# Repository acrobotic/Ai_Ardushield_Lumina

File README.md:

Overview
---
This repository includes the Eagle design files (schematics and layout) for our
[WS2812B RGB LED Shield for the Arduino Uno][1]. The shield design is based on the
popular WS2812 'smart' LED package, which contains an embedded, costant-current
LED driver (the WS2811).

The shield includes **40 WS2812B LEDs in a 5x8 array configuration**. But, contrary to a traditional
LED matrix, the shield uses a single data line (Digital Pin 8) from the 
Arduino to control brightness and color!  The shield also includes a power 
terminal for using an external supply.

The firmware files along with code samples are also included in this
repository.

Product page
---
Please consider buying products from Acrobotic to help fund future Open-Source
projects like this! We'll always put our best effort in every project, and
release all our design files and code for you to use.

[Tutorials, technical details, and more information about this product can be
found here: http://acrobotic.com/catalog/product/view/id/69][1]

On our store, we also [carry a 10-pack][2] of WS2812B RGB LEDs for you to use 
on your next project!

License Information
---

All contents of this repository are licensed under a [Creative Commons
Attribution-ShareAlike 3.0 Unported
License](http://creativecommons.org/licenses/by-sa/3.0/).

[1]: http://acrobotic.com/catalog/product/view/id/69 "Ardushield Lumina"
[2]: http://acrobotic.com/catalog/product/view/id/45 "WS2812B RGB LED - 10-Pack"

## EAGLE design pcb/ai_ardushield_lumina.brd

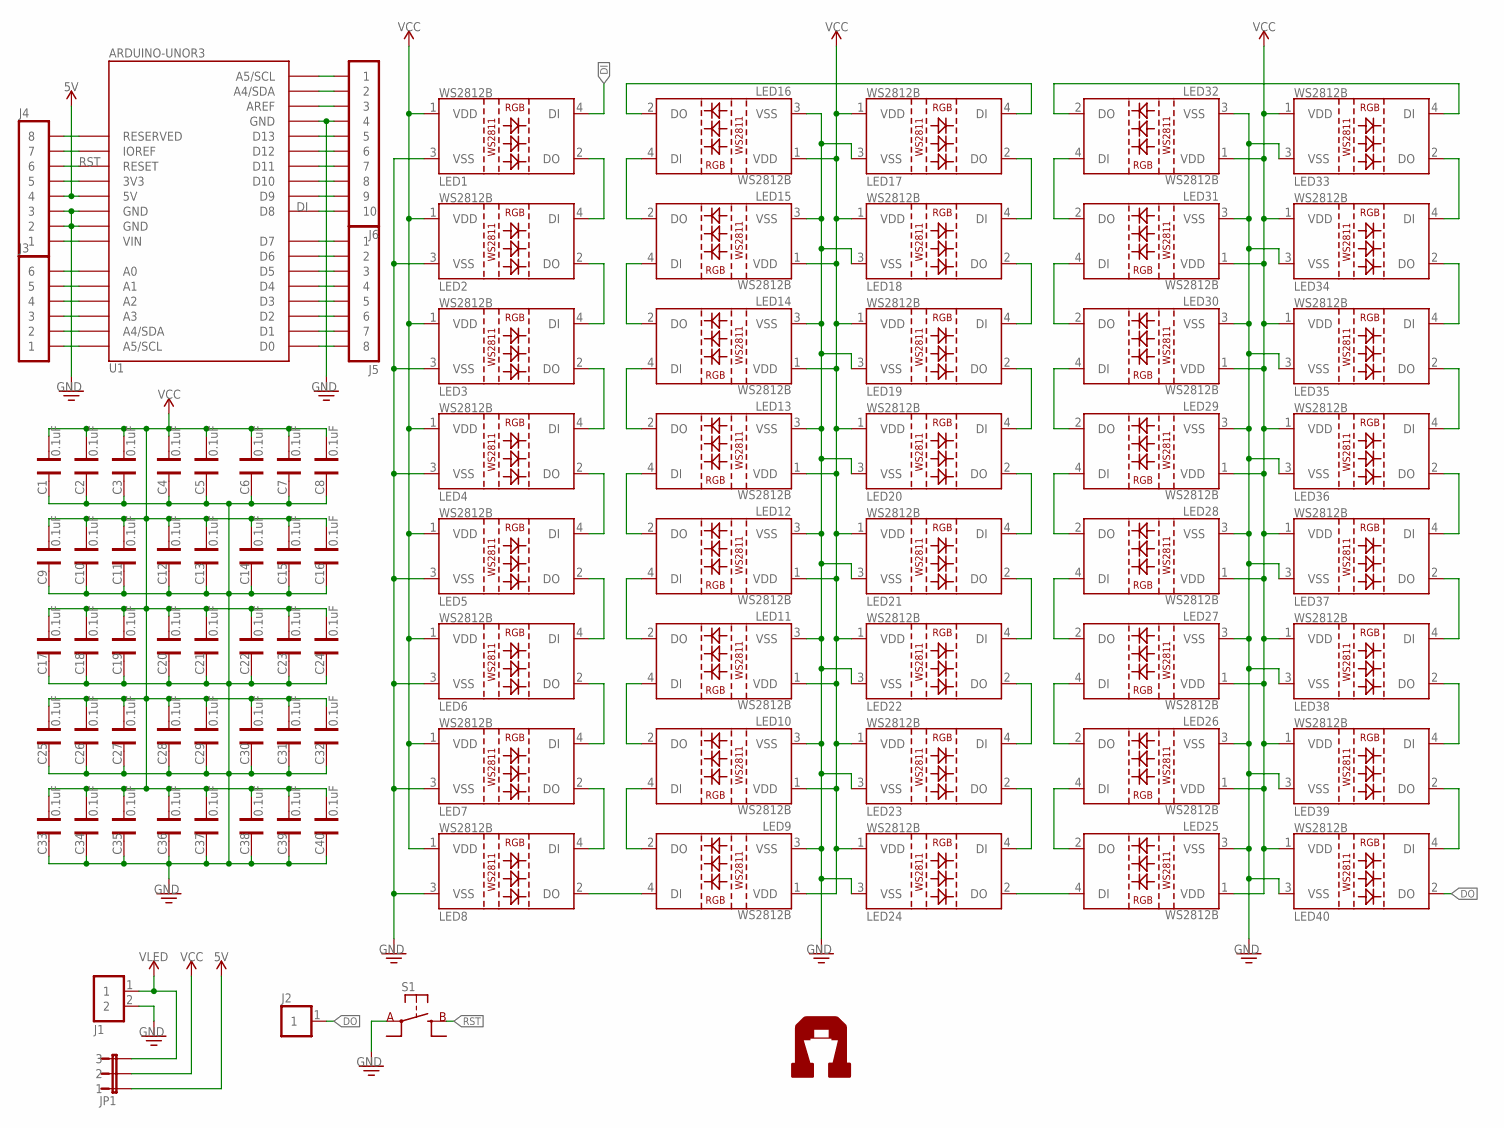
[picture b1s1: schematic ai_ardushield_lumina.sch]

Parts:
C1, C2, C3, C4, C5, C6, C7, C8, C9, C10, C11, C12, C13, C14, C15, C16, C17, C18, C19, C20, C21, C22, C23, C24, C25, C26, C27, C28, C29, C30, C31, C32, C33, C34, C35, C36, C37, C38, C39, C40: 0.1uF; CAP-0603
J1: 1X02ST; 1X02-ST
J2: 1X01
J3: 1X06
J4, J5: 1X08
J6: 1X10
JP1: 1X03-PJ; 1X03
LED1, LED2, LED3, LED4, LED5, LED6, LED7, LED8, LED9, LED10, LED11, LED12, LED13, LED14, LED15, LED16, LED17, LED18, LED19, LED20, LED21, LED22, LED23, LED24, LED25, LED26, LED27, LED28, LED29, LED30, LED31, LED32, LED33, LED34, LED35, LED36, LED37, LED38, LED39, LED40: LED-WS2812B
S1: SW-SPSTSMD06X06; SW-SPST-SMD06X06
U1: ARDUINOUNOR3-STRAIGHT; UNOR3-STRAIGHT
U$9: AI-LOGOL; AI-LOGO-L

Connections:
5V: J4.4, JP1.1, U1.5V
DI: J6.10, LED1.4 (DI), U1.D8
DO: J2.1, LED40.2 (DO)
GND: C1.2, C2.2, C3.2, C4.2, C5.2, C6.2, C7.2, C8.2, C9.2, C10.2, C11.2, C12.2, C13.2, C14.2, C15.2, C16.2, C17.2, C18.2, C19.2, C20.2, C21.2, C22.2, C23.2, C24.2, C25.2, C26.2, C27.2, C28.2, C29.2, C30.2, C31.2, C32.2, C33.2, C34.2, C35.2, C36.2, C37.2, C38.2, C39.2, C40.2, J1.2, J4.2, J4.3, J6.4, LED1.3 (VSS), LED2.3 (VSS), LED3.3 (VSS), LED4.3 (VSS), LED5.3 (VSS), LED6.3 (VSS), LED7.3 (VSS), LED8.3 (VSS), LED9.3 (VSS), LED10.3 (VSS), LED11.3 (VSS), LED12.3 (VSS), LED13.3 (VSS), LED14.3 (VSS), LED15.3 (VSS), LED16.3 (VSS), LED17.3 (VSS), LED18.3 (VSS), LED19.3 (VSS), LED20.3 (VSS), LED21.3 (VSS), LED22.3 (VSS), LED23.3 (VSS), LED24.3 (VSS), LED25.3 (VSS), LED26.3 (VSS), LED27.3 (VSS), LED28.3 (VSS), LED29.3 (VSS), LED30.3 (VSS), LED31.3 (VSS), LED32.3 (VSS), LED33.3 (VSS), LED34.3 (VSS), LED35.3 (VSS), LED36.3 (VSS), LED37.3 (VSS), LED38.3 (VSS), LED39.3 (VSS), LED40.3 (VSS), S1.A@1 (A), S1.A@2 (A), U1.GND@1 (GND), U1.GND@2 (GND), U1.GND@3 (GND)
unnamed: LED1.2 (DO), LED2.4 (DI)
unnamed: LED2.2 (DO), LED3.4 (DI)
unnamed: LED3.2 (DO), LED4.4 (DI)
unnamed: LED4.2 (DO), LED5.4 (DI)
unnamed: LED5.2 (DO), LED6.4 (DI)
unnamed: LED6.2 (DO), LED7.4 (DI)
unnamed: LED7.2 (DO), LED8.4 (DI)
unnamed: LED8.2 (DO), LED9.4 (DI)
unnamed: LED9.2 (DO), LED10.4 (DI)
unnamed: LED10.2 (DO), LED11.4 (DI)
unnamed: LED11.2 (DO), LED12.4 (DI)
unnamed: LED12.2 (DO), LED13.4 (DI)
unnamed: LED13.2 (DO), LED14.4 (DI)
unnamed: LED14.2 (DO), LED15.4 (DI)
unnamed: LED15.2 (DO), LED16.4 (DI)
unnamed: LED16.2 (DO), LED17.4 (DI)
unnamed: LED17.2 (DO), LED18.4 (DI)
unnamed: LED18.2 (DO), LED19.4 (DI)
unnamed: LED19.2 (DO), LED20.4 (DI)
unnamed: LED20.2 (DO), LED21.4 (DI)
unnamed: LED21.2 (DO), LED22.4 (DI)
unnamed: LED22.2 (DO), LED23.4 (DI)
unnamed: LED23.2 (DO), LED24.4 (DI)
unnamed: LED24.2 (DO), LED25.4 (DI)
unnamed: LED25.2 (DO), LED26.4 (DI)
unnamed: LED26.2 (DO), LED27.4 (DI)
unnamed: LED27.2 (DO), LED28.4 (DI)
unnamed: LED28.2 (DO), LED29.4 (DI)
unnamed: LED29.2 (DO), LED30.4 (DI)
unnamed: LED30.2 (DO), LED31.4 (DI)
unnamed: LED31.2 (DO), LED32.4 (DI)
unnamed: LED32.2 (DO), LED33.4 (DI)
unnamed: LED33.2 (DO), LED34.4 (DI)
unnamed: LED34.2 (DO), LED35.4 (DI)
unnamed: LED35.2 (DO), LED36.4 (DI)
unnamed: LED36.2 (DO), LED37.4 (DI)
unnamed: J4.8, U1.RESERVED
unnamed: J4.7, U1.IOREF
unnamed: J4.5, U1.3V3
unnamed: J4.1, U1.VIN
unnamed: J3.6, U1.A0
unnamed: J3.5, U1.A1
unnamed: J3.4, U1.A2
unnamed: J3.3, U1.A3
unnamed: J3.2, U1.A4/SDA@1 (A4/SDA)
unnamed: J3.1, U1.A5/SCL@1 (A5/SCL)
unnamed: J5.8, U1.D0
unnamed: J5.7, U1.D1
unnamed: J5.6, U1.D2
unnamed: J5.5, U1.D3
unnamed: J5.4, U1.D4
unnamed: J5.3, U1.D5
unnamed: J6.1, U1.A5/SCL@2 (A5/SCL)
unnamed: J6.2, U1.A4/SDA@2 (A4/SDA)
unnamed: J6.3, U1.AREF
unnamed: J6.5, U1.D13
unnamed: J6.6, U1.D12
unnamed: J6.7, U1.D11
unnamed: J6.8, U1.D10
unnamed: J6.9, U1.D9
unnamed: J5.1, U1.D7
unnamed: J5.2, U1.D6
unnamed: LED37.2 (DO), LED38.4 (DI)
unnamed: LED38.2 (DO), LED39.4 (DI)
unnamed: LED39.2 (DO), LED40.4 (DI)
RST: J4.6, S1.B@1 (B), S1.B@2 (B), U1.RESET
VCC: C1.1, C2.1, C3.1, C4.1, C5.1, C6.1, C7.1, C8.1, C9.1, C10.1, C11.1, C12.1, C13.1, C14.1, C15.1, C16.1, C17.1, C18.1, C19.1, C20.1, C21.1, C22.1, C23.1, C24.1, C25.1, C26.1, C27.1, C28.1, C29.1, C30.1, C31.1, C32.1, C33.1, C34.1, C35.1, C36.1, C37.1, C38.1, C39.1, C40.1, JP1.2, LED1.1 (VDD), LED2.1 (VDD), LED3.1 (VDD), LED4.1 (VDD), LED5.1 (VDD), LED6.1 (VDD), LED7.1 (VDD), LED8.1 (VDD), LED9.1 (VDD), LED10.1 (VDD), LED11.1 (VDD), LED12.1 (VDD), LED13.1 (VDD), LED14.1 (VDD), LED15.1 (VDD), LED16.1 (VDD), LED17.1 (VDD), LED18.1 (VDD), LED19.1 (VDD), LED20.1 (VDD), LED21.1 (VDD), LED22.1 (VDD), LED23.1 (VDD), LED24.1 (VDD), LED25.1 (VDD), LED26.1 (VDD), LED27.1 (VDD), LED28.1 (VDD), LED29.1 (VDD), LED30.1 (VDD), LED31.1 (VDD), LED32.1 (VDD), LED33.1 (VDD), LED34.1 (VDD), LED35.1 (VDD), LED36.1 (VDD), LED37.1 (VDD), LED38.1 (VDD), LED39.1 (VDD), LED40.1 (VDD)
VLED: J1.1, JP1.3

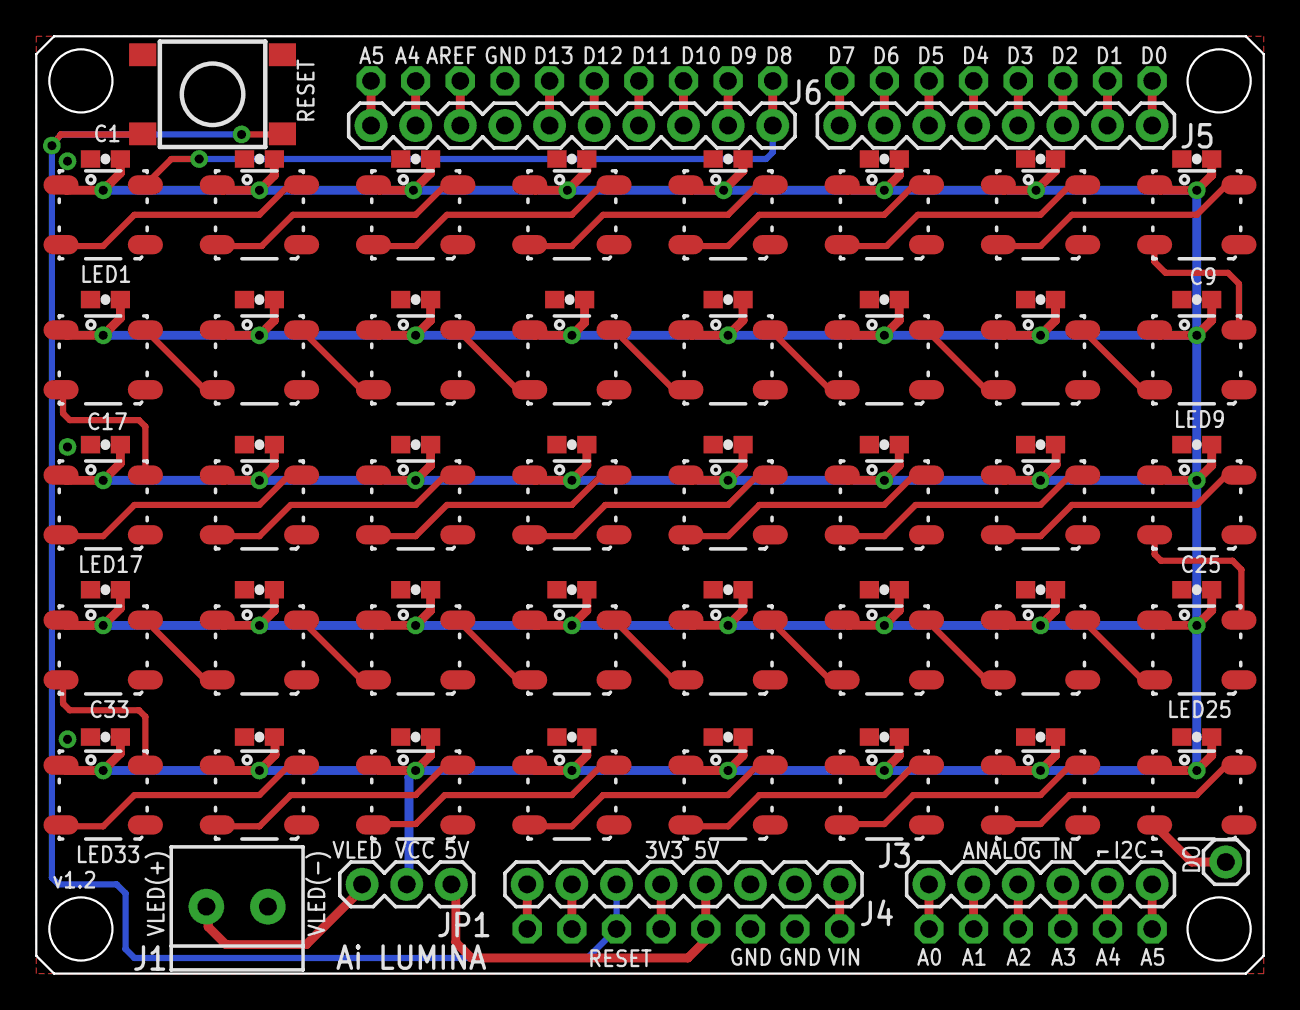
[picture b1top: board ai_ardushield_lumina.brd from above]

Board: 2 copper layers, 69.8 x 53.3 mm, 90 parts (1 on the bottom side), 72 nets.

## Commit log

2013-09-25 first commit.
2013-10-16 Updated to latest libraries. New Gerbers.
2013-10-16 Fixed a typo in README.md. Added .pdf file for schematic.
2013-10-16 First commit to pages branch
2013-10-16 deleting old files
2013-10-25 Modified the routing quite a bit.
2013-10-25 updating schematic pdf.
2013-10-25 adding BOM.
2013-11-19 Changed design to use WS2812Bs
2014-07-28 updating firmware
2015-05-30 adding pnp files
2019-02-14 https://github.com/oscarg933/Ai_PixelFlags/pulse
    https://github.com/oscarg933/Ai_PixelFlags/pulse
2019-02-14 Create Insert-fire-memory
2019-02-14 https://github.com/oscarg933/Ai_Ardushield_Lumina/tree/Hackerspray.git
    https://github.com/oscarg933/Ai_Ardushield_Lumina/tree/Hackerspray.git
